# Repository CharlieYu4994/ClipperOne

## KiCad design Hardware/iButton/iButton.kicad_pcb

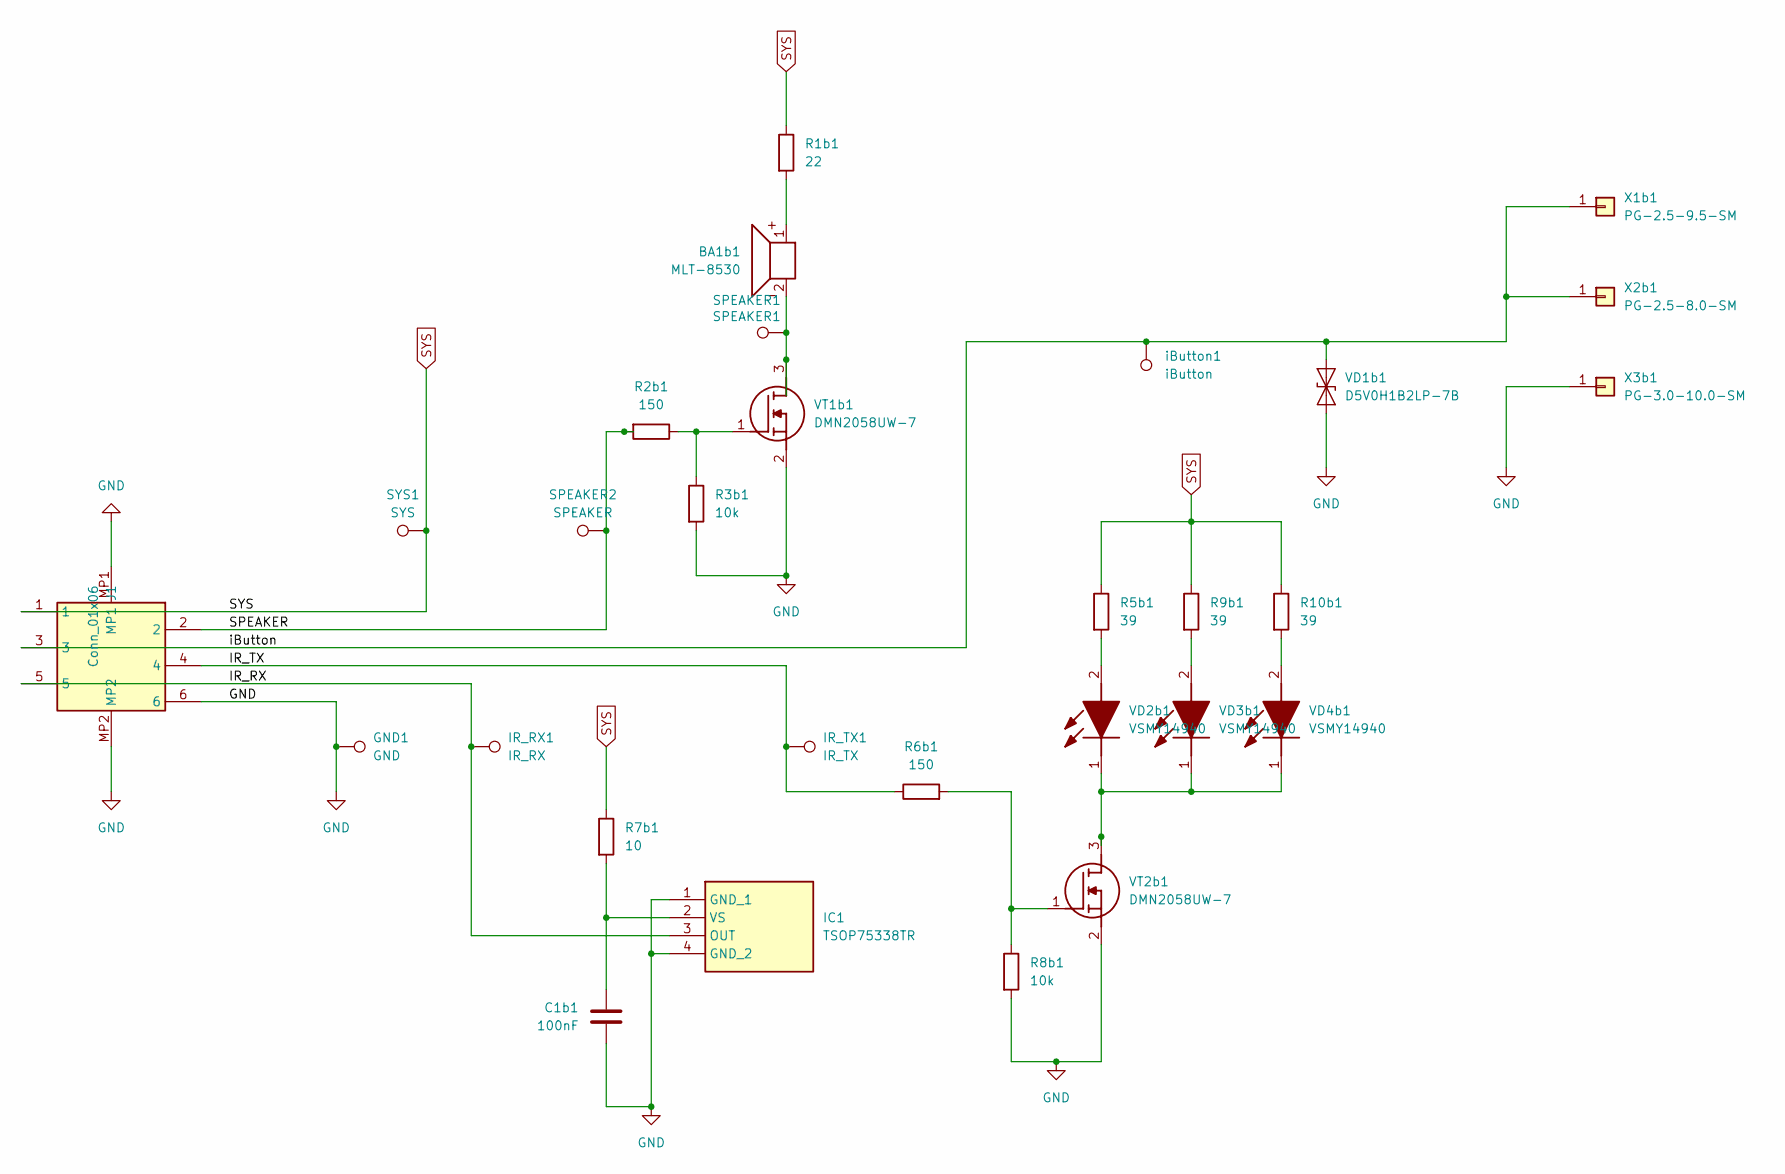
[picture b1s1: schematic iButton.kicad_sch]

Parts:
BA1b1: MLT-8530; MLT8530
C1b1: 100nF; C_0402_1005Metric
GND1: GND; TestPoint_Pad_D1.0mm
IC1: TSOP75338TR; Manufacturer_Part_Number TSOP75338TR; Mouser Part Number 78-TSOP75338TR
IR_RX1: IR_RX; TestPoint_Pad_D1.0mm
IR_TX1: IR_TX; TestPoint_Pad_D1.0mm
J1: Conn_01x06; AFC11S06ICC00; Manufacturer_Part_Number AFC11-S06ICC-00
R1b1: 22; R_0402_1005Metric
R2b1, R6b1: 150; R_0402_1005Metric
R3b1, R8b1: 10k; R_0402_1005Metric
R5b1, R9b1, R10b1: 39; R_0402_1005Metric
R7b1: 10; R_0402_1005Metric
SPEAKER1: SPEAKER1; TestPoint_Pad_D1.0mm
SPEAKER2: SPEAKER; TestPoint_Pad_D1.0mm
SYS1: SYS; TestPoint_Pad_D1.0mm
VD1b1: D5V0H1B2LP-7B; D5V0H1B2LP7B
VD2b1, VD3b1, VD4b1: VSMY14940; LEDC3012X261N; Manufacturer_Part_Number VSMY14940; Mouser Part Number 782-VSMY14940
VT1b1, VT2b1: DMN2058UW-7; SOT65P210X110-3N; Manufacturer_Part_Number AO3400A
X1b1: PG-2.5-9.5-SM; TestPoint_Pad_D2.0mm
X2b1: PG-2.5-8.0-SM; TestPoint_Pad_D2.0mm
X3b1: PG-3.0-10.0-SM; TestPoint_Pad_D2.0mm
iButton1: iButton; TestPoint_Pad_D1.0mm

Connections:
/IR_RX: IC1.3 (OUT), IR_RX1.1, J1.5
/IR_TX: IR_TX1.1, J1.4, R6b1.1
/SPEAKER: J1.2, R2b1.2, SPEAKER2.1
/iButton: J1.3, VD1b1.2 (A2), X1b1.1, X2b1.1, iButton1.1
GND: C1b1.2, GND1.1, IC1.1 (GND_1), IC1.4 (GND_2), J1.6, J1.MP1, J1.MP2, R3b1.2, R8b1.2, VD1b1.1 (A1), VT1b1.2 (S), VT2b1.2 (S), X3b1.1
unnamed: BA1b1.1 (+), R1b1.2
unnamed: BA1b1.2 (-), SPEAKER1.1, VT1b1.3 (D)
unnamed: C1b1.1, IC1.2 (VS), R7b1.2
unnamed: R5b1.2, VD2b1.2 (A)
unnamed: VD2b1.1 (K), VD3b1.1 (K), VD4b1.1 (K), VT2b1.3 (D)
unnamed: R9b1.2, VD3b1.2 (A)
unnamed: R10b1.2, VD4b1.2 (A)
unnamed: R2b1.1, R3b1.1, VT1b1.1 (G)
unnamed: R6b1.2, R8b1.1, VT2b1.1 (G)
SYS: J1.1, R1b1.1, R5b1.1, R7b1.1, R9b1.1, R10b1.1, SYS1.1

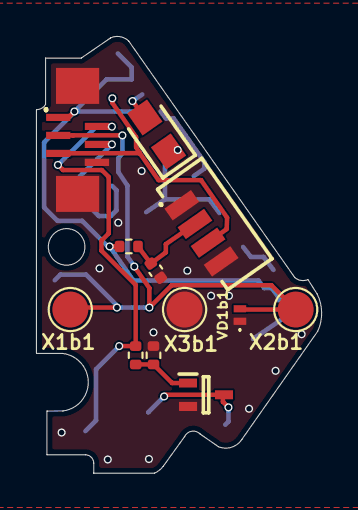
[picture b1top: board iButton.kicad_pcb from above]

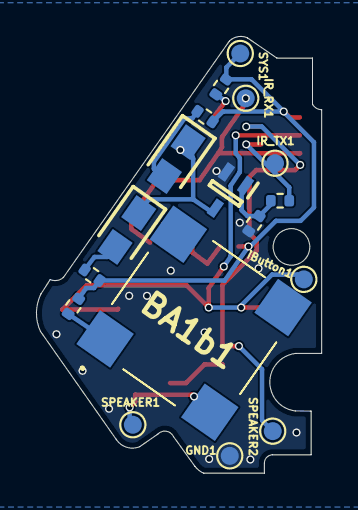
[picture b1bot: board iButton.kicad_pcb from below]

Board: 2 copper layers, 15.8 x 24.3 mm, 29 parts (17 on the bottom side), 15 nets.

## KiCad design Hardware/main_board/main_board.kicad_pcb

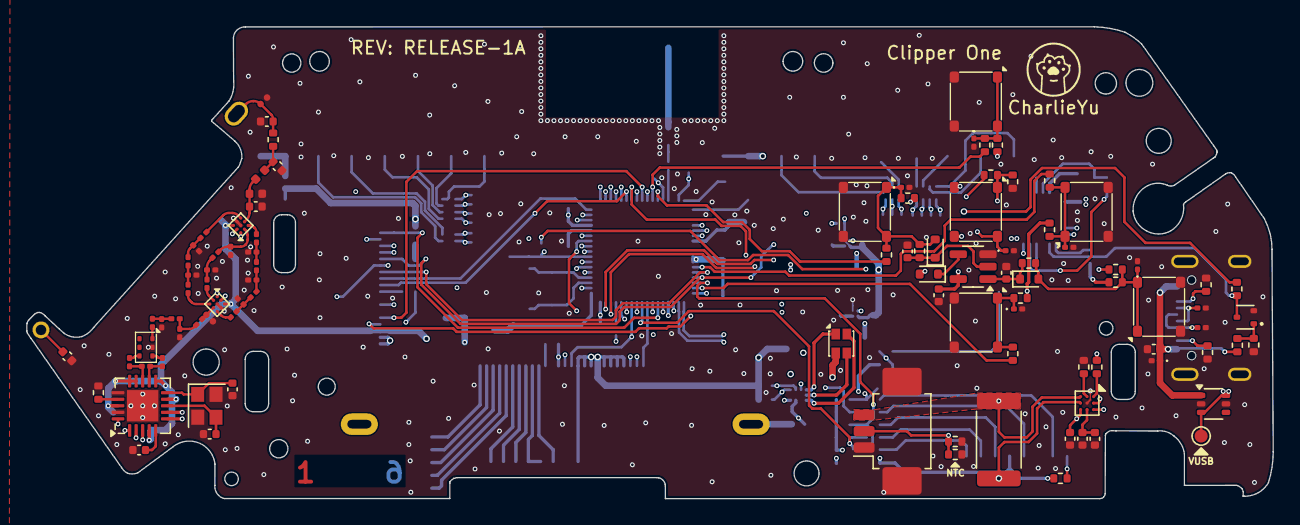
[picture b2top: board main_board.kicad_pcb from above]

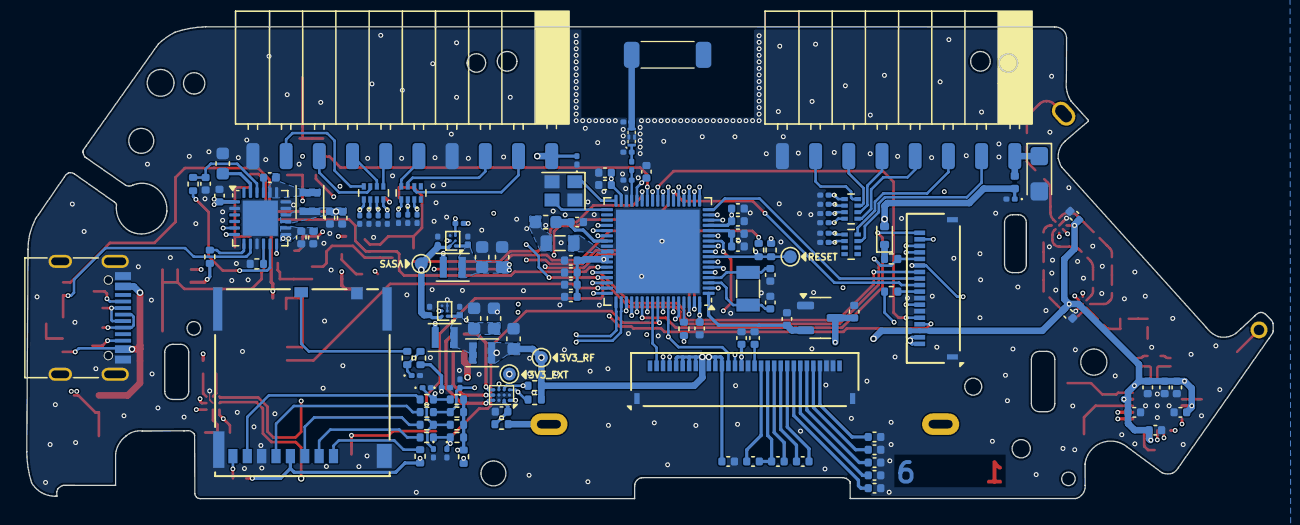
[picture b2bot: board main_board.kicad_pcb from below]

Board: 6 copper layers, 95.4 x 36.1 mm, 238 parts (136 on the bottom side), 165 nets.

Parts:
AE1: CrossAir C3; CrossAir-C3
AE2: Sub 1G; ANT_SUB1G
C1, C7, C11, C28: 4.7uF; C_0402_1005Metric
C2, C3, C4, C5, C8, C13, C40, C41, C42, C43, C44, C45, C46, C66, C69, C80, C82: 100nF; C_0402_1005Metric
C6, C70: 100pF; C_0402_1005Metric
C9, C12, C18, C24, C32, C33: 1uF; C_0402_1005Metric
C10, C54, C55: 10nF; C_0402_1005Metric
C14: 0.3pF; C_0201_0603Metric
C15: 0.8pF; C_0201_0603Metric
C16, C17: 18pF; C_0402_1005Metric
C19: 47nF; C_0402_1005Metric
C20, C21, C26, C27, C67, C68: 10uF; C_0402_1005Metric
C22: 470nF; C_0402_1005Metric
C23, C73, C79: 2.2uF; C_0402_1005Metric
C25, C31, C37, C38: 10uF; C_0603_1608Metric
C29, C35: 1uF; C_0201_0603Metric
C30, C36: 4.7uF; C_0603_1608Metric
C34, C39: 2.2uF; C_0201_0603Metric
C47, C49: 100pF; C_0201_0603Metric
C48: 0.6pF; C_0201_0603Metric
C50, C56, C57, C65: TBD; C_0201_0603Metric
C51: 1.2pF; C_0201_0603Metric
C52, C53: 9pF; C_0402_1005Metric
C58, C62, C63, C71, C72, C74, C75, C76, C77, C78, C83: TBD; C_0402_1005Metric
C59, C60: 10pF; C_0201_0603Metric
C61: 22pF; C_0201_0603Metric
C64: 8.2pF; C_0201_0603Metric
C81: TBD; CP_EIA-3216-18_Kemet-A
D1, D2, D3, D4, D5, D6, D11, D12, D13, D14, D15, D16, D18, D19, D20, D21, D22, D23, D24, D25, D26, D27, D28, D29, D30, D31, D32, D33, D34, D35: TVS; D_0201_0603Metric
D7, D8, D9, D17: 1N4148; D_SOD-523
D10: LED_RBGA; LTST-C19HE1WT_LTO
F1: 2A; Fuse_0402_1005Metric
FL1: DLF162500LT-5028A1; DLF162500LT
J1: BATT; Molex_PicoBlade_53261-0371_1x03-1MP_P1.25mm_Horizontal
J2: LCD; CONN30x1_FH34SRJ-30S-0.5SH50_HIR
J3: BACK_LIGHT; ERC12864FAMF03
J4: SD; CONN_503398-1892_MOL
J5: NFC; CONN18x1_FH34SRJ-18S-0.5SH50_HIR
J6: EXT1; PinSocket_1x10_P2.54mm_Horizontal_SMD
J7: EXT0; PinSocket_1x08_P2.54mm_Horizontal_SMD
J8: USB_C; USB_C_Receptacle_G-Switch_GT-USB-7010ASV
L1: 10uH; L_0603_1608Metric
L2: 10uH; L_0805_2012Metric
L3, L20, L21: 2.7nH; L_0201_0603Metric
L4: 1uH; L_Murata_DFE201610P
L5, L6, L7: 470nH; L_Murata_DFE201610P
L8: 3.3nH; L_0201_0603Metric
L9: 6.8nH; L_0201_0603Metric
L10, L11, L13, L15, L19: 0; L_0201_0603Metric
L12: 56nH; L_0201_0603Metric
L14: 27nH; L_0201_0603Metric
L16: 22nH; L_0201_0603Metric
L17: 2.2nH; L_0402_1005Metric
L18: TBD; L_0402_1005Metric
Q1: DMN313DLT; SOT-523
R1, R45, R46, R47, R50: 51R; R_0402_1005Metric
R2, R3, R8, R11, R12, R14, R19, R20, R21, R22, R23, R30, R31: 10K; R_0402_1005Metric
R4: 470R; R_0402_1005Metric
R5: 10m; R_2512_6332Metric
R6, R7, R51, R52: 5.1K; R_0402_1005Metric
R9: 5.23K; R_0402_1005Metric
R10: 30.1K; R_0402_1005Metric
R13: 100R; R_0402_1005Metric
R15: 10K; R_0201_0603Metric
R16: 0R; R_0201_0603Metric
R17: 56K/0.1%; R_0402_1005Metric
R18, R35, R36: 0R; R_0402_1005Metric
R24, R25, R26, R27, R28, R29, R33: 330R; R_0402_1005Metric
R32, R34: 100K; R_0402_1005Metric
R37, R38, R39, R40, R41, R42, R43: 47K; R_0402_1005Metric
R44, R48: 150R; R_0402_1005Metric
R49: 1K; R_0402_1005Metric
RFF**: CharlieYu; charlieyu
RN1, RN2, RN3, RN4: 51R; R_Array_Concave_4x0402
SW1: OK; SW_Push_SPST_NO_Alps_ SKRM
SW2: BACK; SW_Push_SPST_NO_Alps_ SKRM
SW3: RIGHT; SW_Push_SPST_NO_Alps_ SKRM
SW4: LEFT; SW_Push_SPST_NO_Alps_ SKRM
SW5: UP; SW_Push_SPST_NO_Alps_ SKRM
SW6: DOWN; SW_Push_SPST_NO_Alps_ SKRM
T1: B0310J50100AHF
TP1: RST; TestPoint_Pad_D1.0mm
TP12: 5V_USB; TestPoint_Pad_D1.0mm
TP18: VSYS; TestPoint_Pad_D1.0mm
TP20: 3V3_MAIN; TestPoint_Pad_D1.0mm
TP21: 3V3_EXT; TestPoint_Pad_D1.0mm
TP32: Balun; TP_DP
TP33: CC1101_OUT; TP_DP
U1: STM32WB55RGVx; QFN-68-1EP_8x8mm_P0.4mm_EP6.4x6.4mm
U2: BQ27220YZFR; Texas_DSBGA-9_1.62mmx1.58mm_Layout3x3_P0.5mm
U3: BQ25896RTWR; Texas_RTW_WQFN-24-1EP_4x4mm_P0.5mm_EP2.7x2.7mm
U4: RS3221-3.3YF3; SOT-23-3
U5: LM66100DCK; SOT-363_SC-70-6
U6, U7: LM3281YFQR; BGA-6_2x3_1.16x1.435mm
U8: CC1101RGP; Texas_RGP0020H_VQFN-20-1EP_4x4mm_P0.5mm_EP2.4x2.4mm
U9, U10: BGS13S4N9E6327XTSA1; BGA-9_3x3_1.2x1.2mm
U11: NC7SZ32M5X; SOT-23-5
U12: LP5562TMX; BGA-12_4x3_1.6x1.2mm
Y1: 32MHz; Crystal_SMD_2520-4Pin_2.5x2.0mm
Y2: 32.768K; Crystal_SMD_3215-2Pin_3.2x1.5mm
Y3: 26MHz; Crystal_SMD_2520-4Pin_2.5x2.0mm

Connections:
+3.3V: C1.2, C2.2, C3.2, C4.2, C5.2, C6.2, C7.2, C8.2, C9.2, C10.2, C38.2, C40.2, C41.2, C42.2, C43.2, C44.2, C45.2, C54.1, C55.1, C66.1, C69.2, C70.2, J2.5, J2.6, J2.7, J2.8, J2.9, J2.10, J2.11, J2.12, J2.15, J5.3, L7.2, R2.1, R6.2, R7.2, R8.2, R15.1, R19.2, R20.2, R21.2, R22.2, R23.2, R31.2, SW1.2, TP20.1, U1.14 (VDDA), U1.30 (VDD), U1.33 (VDDRF), U1.44 (VDDSMPS), U1.45 (VDD), U1.55 (VDDUSB), U1.68 (VDD), U8.4 (DVDD), U8.9 (AVDD), U8.11 (AVDD), U8.14 (AVDD), U8.15 (AVDD), U8.18 (DGUARD), U9.A3 (VDD), U10.A3 (VDD), U11.5 (VCC)
+3.3V_EXT: C30.2, C31.2, C34.2, D18.2 (A2), J6.1, L5.2, R36.1, TP21.1, U6.A1 (FB)
+3.3V_LDO: C33.2, U1.1 (VBAT), U4.2 (VOUT)
/Buttons/BACK: D2.1 (A1), D7.2 (A), R19.1, R25.2, R32.2, SW2.1
/Buttons/BUTTON_BACK: R25.1, U1.2 (PC13), U3.12 (QON_N)
/Buttons/BUTTON_DOWN: R29.1, U1.50 (PC6)
/Buttons/BUTTON_LEFT: R27.1, U1.29 (PB11)
/Buttons/BUTTON_OK: R24.1, U1.5 (PH3)
/Buttons/BUTTON_RIGHT: R26.1, U1.46 (PB12)
/Buttons/BUTTON_UP: R28.1, U1.28 (PB10)
/Buttons/LEFT: D4.1 (A1), D9.2 (A), R21.1, R27.2, R34.2, SW4.1
/Buttons/RESET: R31.1, R33.1, TP1.1, U1.8 (NRST), U12.C3 (EN_VCC)
/CC1101/CC1101_CS: U1.61 (PD0), U8.7 (CSN)
/CC1101/CC1101_G0: U1.16 (PA1), U8.6 (GDO0)
/CC1101/CC1101_UBAL: R16.2, TP32.1, U9.C2 (RFIN)
/CC1101/RF_SW_0: U1.25 (PC4), U9.A2 (V2), U10.A1 (V1)
/CC1101/RF_SW_1: U8.3 (GD02), U9.A1 (V1), U10.A2 (V2)
/CC1101/SPI_R_MISO: R50.1, U1.64 (PB4), U8.2 (SO)
/CC1101/SPI_R_MOSI: J5.13, R1.2, U8.20 (SI)
/CC1101/SPI_R_SCK: J5.7, U1.20 (PA5), U8.1 (SCLK)
/LCD/DISPLAY_CS: J2.2, U1.59 (PC11)
/LCD/DISPLAY_DI: J2.4, U1.39 (PB1)
/LCD/DISPLAY_RST: J2.3, U1.38 (PB0)
/LCD/LCD_LED: J3.1 (K), U12.A1 (W)
/LCD/SPI_D_MOSI: D12.1 (A1), J2.14, R38.1, R45.1, U1.49 (PB15)
/LCD/SPI_D_SCK: D13.1 (A1), J2.13, R39.1, R46.1, U1.62 (PD1)
/MCU/D+: D35.1 (A1), J8.A6 (D+), J8.B6 (D+), U1.53 (PA12)
/MCU/D-: D34.1 (A1), J8.A7 (D-), J8.B7 (D-), U1.52 (PA11)
/MCU/I2C_SCL: R7.1, U1.24 (PA9), U2.A3 (SCL), U3.5 (SCL), U12.C2 (SCL)
/MCU/I2C_SDA: R6.1, U1.51 (PA10), U2.A2 (SDA), U3.6 (SDA), U12.C1 (SDA)
/MCU/IR_RX: J5.17, U1.15 (PA0)
/MCU/IR_TX: J5.16, U1.7 (PB9)
/MCU/NFC_CS: J5.4, U1.40 (PE4)
/MCU/PA4: D22.1 (A1), RN3.8, U1.19 (PA4)
/MCU/PA6: D21.1 (A1), RN1.5, U1.21 (PA6)
/MCU/PA7: D20.1 (A1), RN1.6, U1.22 (PA7)
/MCU/PB2: D24.1 (A1), RN3.6, U1.27 (PB2)
/MCU/PB3: D23.1 (A1), RN3.7, U1.63 (PB3)
/MCU/PC0: D31.1 (A1), RN4.6, U1.9 (PC0)
/MCU/PC1: D30.1 (A1), RN4.7, U1.10 (PC1)
/MCU/PC3: D25.1 (A1), RN3.5, U1.12 (PC3)
/MCU/PERI_EN: R15.2, U1.18 (PA3), U6.C1 (EN)
/MCU/RFID_CARRIER: J5.18, U1.57 (PA15)
/MCU/RFID_OUT: J5.12, U1.47 (PB13)
/MCU/RFID_PULL: J5.11, U1.17 (PA2)
/MCU/RFID_RF_IN: J5.5, U1.26 (PC5)
/MCU/SD_CD: D15.1 (A1), R41.1, R48.1, U1.58 (PC10)
/MCU/SD_CS: D11.1 (A1), R37.1, R44.1, U1.60 (PC12)
/MCU/SPEAKER: J5.15, U1.6 (PB8)
/MCU/SPI_D_MISO: D14.1 (A1), R40.1, R47.1, U1.11 (PC2)
/MCU/SWCLK: D26.1 (A1), RN2.7, U1.56 (PA14)
/MCU/SWDIO: D27.1 (A1), RN2.6, U1.54 (PA13)
/MCU/UART1_RX: D29.1 (A1), RN4.8, U1.67 (PB7)
/MCU/UART1_TX: D28.1 (A1), RN2.5, U1.66 (PB6)
/MCU/VIBRO: J5.10, U1.23 (PA8)
/MCU/iBTN: D32.1 (A1), J5.14, R49.2, RN4.5, U1.48 (PB14)
/Power/BAT+: C18.2, J1.3, R5.2, U2.C1 (SRP), U2.C3 (BAT)
BAT: C26.2, C27.2, C32.2, R5.1, U2.C2 (SRN), U3.13 (BAT), U3.14 (BAT), U4.3 (VIN)
GND: C1.1, C2.1, C3.1, C4.1, C5.1, C6.1, C7.1, C8.1, C9.1, C10.1, C11.1, C12.1, C13.1, C14.1, C15.1, C16.1, C17.1, C18.1, C20.1, C21.1, C22.1, C23.1, C24.1, C25.1, C26.1, C27.1, C28.1, C29.1, C30.1, C31.1, C32.1, C33.1, C34.1, C35.1, C36.1, C37.1, C38.1, C39.1, C40.1, C41.1, C42.1, C43.1, C44.1, C45.1, C46.2, C50.1, C51.1, C52.1, C53.1, C54.2, C55.2, C56.2, C57.2, C58.2, C59.1, C60.1, C61.1, C62.1, C63.1, C64.1, C65.1, C66.2, C67.1, C68.1, C69.1, C70.1, C71.1, C75.1, C76.1, C77.1, C78.1, C79.1, C80.2, C81.2, C82.2, C83.1, D1.2 (A2), D2.2 (A2), D3.2 (A2), D4.2 (A2), D5.2 (A2), D6.2 (A2), D11.2 (A2), D12.2 (A2), D13.2 (A2), D14.2 (A2), D15.2 (A2), D16.2 (A2), D18.1 (A1), D19.2 (A2), D20.2 (A2), D21.2 (A2), D22.2 (A2), D23.2 (A2), D24.2 (A2), D25.2 (A2), D26.2 (A2), D27.2 (A2), D28.2 (A2), D29.2 (A2), D30.2 (A2), D31.2 (A2), D32.2 (A2), D33.2 (A2), D34.2 (A2), D35.2 (A2), FL1.2 (GND), FL1.4 (GND), J1.1, J1.MP (MountPin), J2.16, J2.28, J2.29, J2.MP (MountPin), J4.6 (VSS), J4.10 (SHIELD), J5.6, J5.8, J5.MP (MountPin), J6.4, J6.10, J7.8, J8.A1 (GND), J8.A12 (GND), J8.B1 (GND), J8.B12 (GND), J8.S1 (SHIELD), L18.1, L21.1, Q1.2 (S), R3.2, R4.1, R10.1, R11.1, R14.1, R17.2, R30.1, R51.1, R52.1, SW2.2, SW3.2, SW4.2, SW5.2, SW6.2, T1.2 (GND), TP32.2, TP33.2, U1.32 (VSSRF), U1.42 (VSSSMPS), U1.69 (VSS), U2.B2 (VSS), U3.2 (PSEL), U3.9 (CE_N), U3.17 (PGND), U3.18 (PGND), U3.25 (PAD), U4.1 (GND), U5.2 (GND), U5.5 (ST), U6.C2 (EPAD), U7.B1 (MODE), U7.C1 (EN), U7.C2 (EPAD), U8.16 (GND), U8.19 (GND), U8.21 (EPAD), U9.B2 (GND), U9.B3 (DGND), U10.B2 (GND), U10.B3 (DGND), U11.3 (GND), U12.A3 (CLK_32K), U12.B1 (A1), U12.B2 (A0), U12.B3 (GND), Y1.2, Y1.4, Y3.2, Y3.4
unnamed: AE1.1 (FEED), FL1.3 (OUT), L21.2
unnamed: AE2.1 (A), C63.2, R18.2, TP33.1
unnamed: AE2.2 (Shield), C83.2
unnamed: C47.2, T1.4 (Bal)
unnamed: C49.2, T1.3 (Bal)
unnamed: C50.2, L8.2, L9.1
unnamed: C51.2, L9.2, R16.1
unnamed: C56.1, L10.2, L11.1
unnamed: C57.1, L11.2, L12.1
unnamed: C59.2, L13.2, L14.1
unnamed: C60.2, L14.2, L15.1
unnamed: C61.2, L15.2, L16.1
unnamed: C62.2, L17.2, R18.1
unnamed: C64.2, L19.2, L20.1
unnamed: D1.1 (A1), R24.2, R30.2, SW1.1
unnamed: D3.1 (A1), R20.1, R26.2, SW3.1
unnamed: D5.1 (A1), R22.1, R28.2, SW5.1
unnamed: D6.1 (A1), R23.1, R29.2, SW6.1
unnamed: C67.2, D7.1 (K), R32.1, U11.1
unnamed: D8.2 (A), R33.2
unnamed: D8.1 (K), U11.4
unnamed: C68.2, D9.1 (K), R34.1, U11.2
unnamed: D10.2 (BK), U12.A4 (B)
unnamed: D10.3 (GK), U12.B4 (G)
unnamed: D10.1 (RK), U12.C4 (R)
unnamed: D16.1 (A1), J4.4 (VDD), R36.2, R37.2, R38.2, R39.2, R40.2, R41.2, R42.2, R43.2
unnamed: D17.1 (K), R49.1
unnamed: C14.2, FL1.1 (IN), L3.1
unnamed: J1.2, R9.2, R10.2, R11.2, U3.11 (TS)
unnamed: C71.2, J2.17
unnamed: C72.2, J2.18
unnamed: C72.1, C73.2, J2.19
unnamed: C73.1, J2.20
unnamed: C74.2, J2.21
unnamed: C74.1, J2.22
unnamed: C75.2, J2.23
unnamed: C76.2, J2.24
unnamed: C77.2, J2.25
unnamed: C78.2, J2.26
unnamed: C79.2, J2.27
unnamed: J3.2 (A), R35.1
unnamed: J4.5 (CLK), R46.2
unnamed: J4.3 (CMD), R45.2
unnamed: J4.7 (DAT0), R47.2
unnamed: J4.8 (DAT1), R42.1
unnamed: J4.1 (DAT2), R43.1
unnamed: J4.2 (DAT3/CD), R44.2
unnamed: J4.9 (DET), R48.2
unnamed: J5.9, R50.2
unnamed: J6.2, RN2.2
unnamed: J6.3, RN2.3
unnamed: J6.5, RN2.4
unnamed: J6.6, RN4.1
unnamed: J6.7, RN4.2
unnamed: J6.8, RN4.3
unnamed: J6.9, RN4.4
unnamed: C81.1, F1.2, J7.1
unnamed: J7.2, RN1.3
unnamed: J7.3, RN1.4
unnamed: J7.4, RN3.1
unnamed: J7.5, RN3.2
unnamed: J7.6, RN3.3
unnamed: J7.7, RN3.4
unnamed: J8.A5 (CC1), R52.2
unnamed: J8.B5 (CC2), R51.2
unnamed: L1.2, L2.1
unnamed: Q1.3 (D), R12.2, U3.8 (OTG_IUSB)
unnamed: Q1.1 (G), R13.2, R14.2
unnamed: L8.1, T1.1 (Unbal)
unnamed: U1.35 (OSC_IN), Y1.3
unnamed: U1.34 (OSC_OUT), Y1.1
unnamed: R1.1, U1.65 (PB5)
unnamed: C16.2, U1.3 (PC14), Y2.2
unnamed: C17.2, U1.4 (PC15), Y2.1
unnamed: C15.2, L3.2, U1.31 (RF1)
unnamed: C11.2, L1.1, U1.41 (VFBSMPS)
unnamed: L2.2, U1.43 (VLXSMPS)
unnamed: C12.2, C13.2, U1.13 (VREF+)
unnamed: R3.1, U2.B1 (BIN)
unnamed: R2.2, U2.A1 (GPOUT)
unnamed: C22.2, C23.2, U2.B3 (VDD)
unnamed: C19.1, U3.21 (BTST)
unnamed: R4.2, U3.10 (ILIM)
unnamed: R8.1, U3.7 (INT)
unnamed: C25.2, U3.23 (PMID)
unnamed: C28.2, R9.1, U3.22 (REGN)
unnamed: L5.1, U6.B2 (SW)
unnamed: C36.2, C37.2, C39.2, L6.2, L7.1, U7.A1 (FB)
unnamed: L6.1, U7.B2 (SW)
unnamed: C46.1, U8.5 (DCOUPL)
unnamed: R17.1, U8.17 (RBIAS)
unnamed: C47.1, C48.1, U8.13 (RF_N)
unnamed: C48.2, C49.1, U8.12 (RF_P)
unnamed: C52.2, U8.8 (XOSC_Q1), Y3.3
unnamed: C53.2, U8.10 (XOSC_Q2), Y3.1
unnamed: L10.1, U9.C1 (RF1)
unnamed: L13.1, U9.C3 (RF2)
unnamed: L19.1, U9.B1 (RF3)
unnamed: L16.2, U10.C1 (RF1)
unnamed: L12.2, U10.C3 (RF2)
unnamed: C65.2, L20.2, U10.B1 (RF3)
unnamed: C58.1, L17.1, L18.2, U10.C2 (RFIN)
SW: C19.2, L4.1, U3.19 (SW), U3.20 (SW)
VBUS: C82.1, D33.1 (A1), J8.A4 (VBUS), J8.A9 (VBUS), J8.B4 (VBUS), J8.B9 (VBUS), R13.1, U5.1 (VIN)
VSYS: C20.2, C21.2, C29.2, C35.2, C80.1, D10.4 (A), L4.2, R12.1, R35.2, TP18.1, U3.15 (SYS), U3.16 (SYS), U6.A2 (VIN), U6.B1 (MODE), U7.A2 (VIN), U12.A2 (VDD)
VUSB: C24.2, D17.2 (A), D19.1 (A1), F1.1, J5.1, J5.2, TP12.1, U3.1 (VBUS), U5.3 (~CE), U5.6 (VOUT)

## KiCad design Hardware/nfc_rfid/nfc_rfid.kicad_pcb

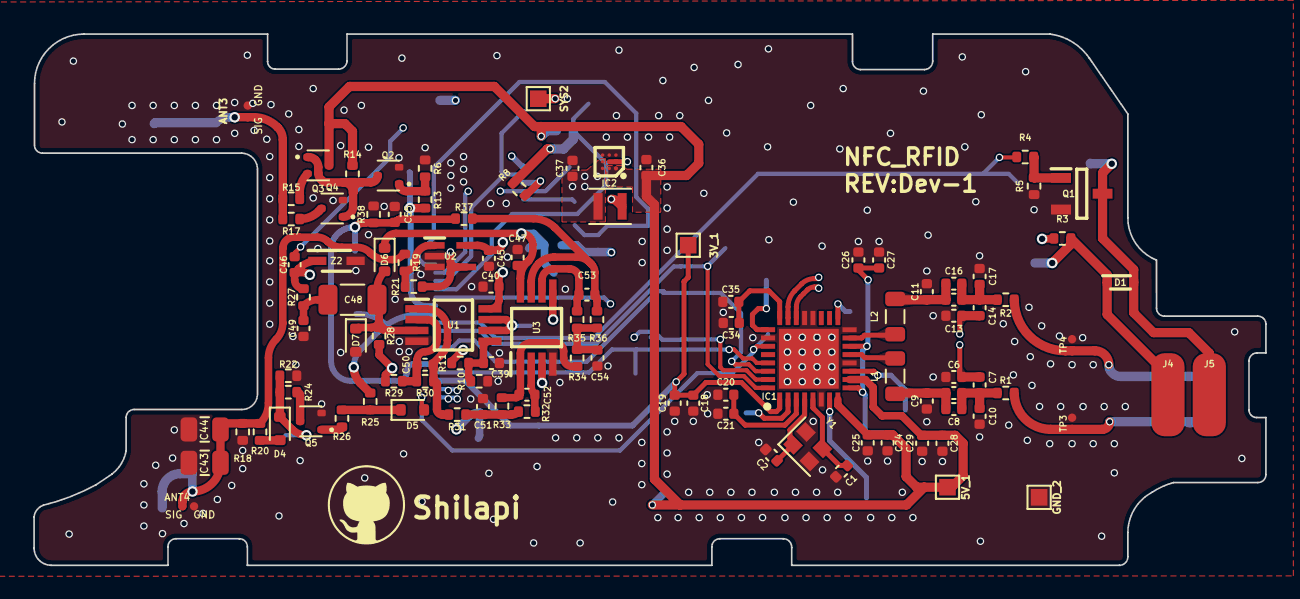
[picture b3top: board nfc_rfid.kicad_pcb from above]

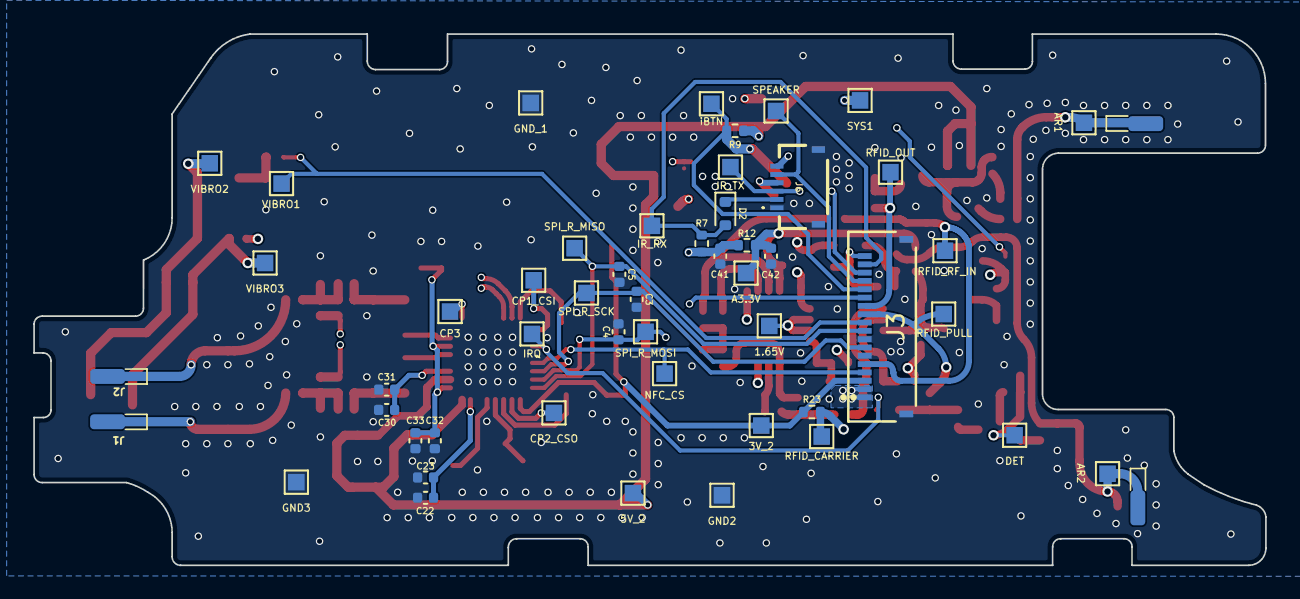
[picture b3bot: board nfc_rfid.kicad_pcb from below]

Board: 4 copper layers, 74.1 x 32.0 mm, 158 parts (52 on the bottom side), 68 nets.

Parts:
C1, C2: 6pF; C_0402_1005Metric
C3, C4, C5, C12, C15, C50: C; C_0402_1005Metric
C6, C8, C13, C16, C52, C53, C55: 100pF; C_0402_1005Metric
C7, C14: 10pF; C_0402_1005Metric
C9, C11: 680pF; C_0402_1005Metric
C10, C17: 62pF; C_0402_1005Metric
C18, C20, C22, C24, C26, C28, C30, C32, C34, C46: 10nF; C_0402_1005Metric
C19, C21, C23, C25, C27, C29, C31, C33, C35: 2.2uF; C_0402_1005Metric
C36: 22uF; C_0402_1005Metric
C37: 10uF; C_0402_1005Metric
C39, C41, C42: 1uF; C_0402_1005Metric
C40, C45, C47: 100nF; C_0402_1005Metric
C43: 3.3nF; C_0805_2012Metric
C44: C; C_0805_2012Metric
C48: 220nF; C_1206_3216Metric
C49: 1nF; C_0402_1005Metric
C51, C54: 4.7nF; C_0402_1005Metric
D1: 1N4148X-TP; SODFL1608X70N
D2, D4, D5, D6, D7: 1N4148WT; D_SOD-523
IC1: ST25R3916-AQWT; QFN50P500X500X100-33N-D
IC2: FAN48610UC50X; BGA9C40P3X3_122X122X62
J1, J2, J7, J8: BW0033AG-L3.4W0.9H1.8; SMD_L3.4-W0.9
J3: HC-FPC-05-09-18RLTAG; CONN18x1_FH34SRJ-18S-0.5SH50_HIR
J4: +; TestPoint_Pad_3.0x2.0mm_round_corner_no_silkscreen
J5: -; TestPoint_Pad_3.0x2.0mm_round_corner_no_silkscreen
J6: AFH34-S06FIA-1H; AFH34S06FIA1H
L1, L2: 270nH; L_0805_2012Metric
L3: 470nH; L_Murata_DFE201610P
Q1: AO3400A; SOT95P280X125-3N
Q2, Q4: DMN2004TK-7; SOT-523
Q3: DMP2004TK-7; SOT-523
Q5: DMN5L06TK-7; SOT-523
R1, R2: 0Ω; R_0402_1005Metric
R3: 22; R_0402_1005Metric
R4: 150; R_0402_1005Metric
R5, R6, R7, R23, R33, R36: 10k; R_0402_1005Metric
R8, R13: 51; R_0402_1005Metric
R9: 47k; R_0402_1005Metric
R10, R11, R37: 33k; R_0402_1005Metric
R12: 10; R_0402_1005Metric
R14: 510; R_0402_1005Metric
R15, R17: 4.7; R_0402_1005Metric
R18, R21: R; R_0402_1005Metric
R19, R22: 330k; R_0402_1005Metric
R20: 0; R_0402_1005Metric
R24: 330; R_0402_1005Metric
R25, R26: 220; R_0402_1005Metric
R27: 5.1k; R_0402_1005Metric
R28: 1M; R_0402_1005Metric
R29, R31, R32, R34, R35: 1k; R_0402_1005Metric
R30: 4.7k; R_0402_1005Metric
R38: 20k; R_0402_1005Metric
TP1: CP1_CSI; TestPoint_Pad_1.0x1.0mm
TP2: CP2_CSO; TestPoint_Pad_1.0x1.0mm
TP3: ANT1; TP_DP
TP4: ANT2; TP_DP
TP5: CP3; TestPoint_Pad_1.0x1.0mm
TP6: IR_RX; TestPoint_Pad_1.0x1.0mm
TP7: IR_TX; TestPoint_Pad_1.0x1.0mm
TP8: SPEAKER; TestPoint_Pad_1.0x1.0mm
TP9: iBTN; TestPoint_Pad_1.0x1.0mm
TP10: SPI_R_MOSI; TestPoint_Pad_1.0x1.0mm
TP11: RFID_OUT; TestPoint_Pad_1.0x1.0mm
TP12: RFID_PULL; TestPoint_Pad_1.0x1.0mm
TP13: SPI_R_MISO; TestPoint_Pad_1.0x1.0mm
TP14: SPI_R_SCK; TestPoint_Pad_1.0x1.0mm
TP15: RFID_RF_IN; TestPoint_Pad_1.0x1.0mm
TP16: NFC_CS; TestPoint_Pad_1.0x1.0mm
TP17: VIBRO1; TestPoint_Pad_1.0x1.0mm
TP18: RFID_CARRIER; TestPoint_Pad_1.0x1.0mm
TP19: GND2; TestPoint_Pad_1.0x1.0mm
TP20: GND3; TestPoint_Pad_1.0x1.0mm
TP21: VIBRO3; TestPoint_Pad_1.0x1.0mm
TP22: VIBRO2; TestPoint_Pad_1.0x1.0mm
TP23: SYS1; TestPoint_Pad_1.0x1.0mm
TP24: SYS2; TestPoint_Pad_1.0x1.0mm
TP25: 5V_1; TestPoint_Pad_1.0x1.0mm
TP26: 5V_2; TestPoint_Pad_1.0x1.0mm
TP27: 3V_1; TestPoint_Pad_1.0x1.0mm
TP28: 3V_2; TestPoint_Pad_1.0x1.0mm
TP29: GND_1; TestPoint_Pad_1.0x1.0mm
TP30: GND_2; TestPoint_Pad_1.0x1.0mm
TP33: 1.65V; TestPoint_Pad_1.0x1.0mm
TP34: A3.3V; TestPoint_Pad_1.0x1.0mm
TP35: AR1; TestPoint_Pad_1.0x1.0mm
TP36: AR2; TestPoint_Pad_1.0x1.0mm
TP37: ANT3; TP_DP
TP38: ANT4; TP_DP
TP39: DET; TestPoint_Pad_1.0x1.0mm
TP40: IRQ; TestPoint_Pad_1.0x1.0mm
U1, U3: LMV358AIDGKR; SOP65P490X110-8N
U2: LMV331IDCKR; SOT65P210X110-5N
Y1: CF4027M12010001; Crystal_SMD_2016-4Pin_2.0x1.6mm
Z2: BZT52C33S-TP; SOD2512X115N

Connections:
+1.65V: R28.1, R29.2, TP33.1, U1.6 (-), U1.7, U3.3 (+), U3.5 (+)
+3.3V: C18.1, C19.1, C41.1, IC1.1 (VDD_IO), J3.3, R7.1, R12.1, R23.2, TP27.1, TP28.1
+5V: C24.1, C25.1, C28.1, C29.1, C36.1, IC1.8 (VDD), IC1.10 (VDD_TX), IC2.A1 (VOUT_1), IC2.A2 (VOUT_2), Q3.3 (D), R9.1, R14.1, TP25.1, TP26.1
/NFC/EXT_LM: IC1.17 (EXT_LM), TP5.1
/NFC/NFC_ANT1: J1.1, R1.2, TP3.1
/NFC/NFC_ANT2: J2.1, R2.2, TP4.1
/NFC/NFC_CS: IC1.29 (BSS), J3.4, TP16.1
/NFC/NFC_IRQ: D5.2 (A), IC1.27 (IRQ), TP40.1
/NFC/RFI_N: C13.1, C14.1, IC1.23 (RFI2)
/NFC/RFI_P: C6.1, C7.1, IC1.22 (RFI1)
/NFC/SPI_R_MISO: C5.1, IC1.32 (MISO), J3.9, TP13.1
/NFC/SPI_R_MOSI: C4.1, IC1.31 (MOSI), J3.13, TP10.1
/NFC/SPI_R_SCK: C3.1, IC1.30 (SCL), J3.7, TP14.1
/Peripheral/IR_RX: D2.2 (A), J3.17, R7.2, TP6.1
/Peripheral/RFID_CARRIER: C46.1, D4.1 (K), J3.18, R21.2, R22.1, R23.1, R24.2, R27.1, TP18.1, TP39.1, U2.4, Z2.1 (K)
/Peripheral/RFID_OUT: J3.12, R13.1, TP11.1
/Peripheral/RFID_PULL: J3.11, R25.1, TP12.1
/Peripheral/RFID_RF_IN: C55.2, J3.5, R37.2, R38.1, TP15.1
/Peripheral/iBTN: C46.2, J3.14, R8.1, R9.2, TP9.1
/RFID_iBTN/IR_TX: J3.16, J6.3, TP7.1
/RFID_iBTN/SPEAKER: J3.15, J6.5, TP8.1
/RFID_iBTN/TSOP_RX: D2.1 (K), J6.2
A+3.3V: C40.2, C42.1, C45.1, C47.2, D6.1 (K), R11.1, R12.2, TP34.1, U1.8 (V+), U2.5 (V+), U3.8 (V+)
GND: C1.1, C2.1, C3.2, C4.2, C5.2, C6.2, C9.2, C10.2, C11.2, C13.2, C17.1, C18.2, C19.2, C20.2, C21.2, C22.2, C23.2, C24.2, C25.2, C26.2, C27.2, C28.2, C29.2, C30.2, C31.2, C32.2, C33.2, C34.2, C35.2, C36.2, C37.2, C39.2, C40.1, C41.2, C42.2, C43.2, C44.2, C45.2, C47.1, C49.2, C51.1, C54.1, C55.1, D7.2 (A), IC1.6 (GND_D), IC1.12 (GND_DR_1), IC1.16 (GND_DR_2), IC1.20 (I2C_EN), IC1.21 (VSS), IC1.26 (GND_A), IC1.33 (EPAD), IC2.C1 (PGND_1), IC2.C2 (PGND_2), IC2.C3 (AGND), J3.6, J3.8, J3.19, J3.20, J6.1, J6.7 (MP1), J6.8 (MP2), Q1.2 (S), Q2.2 (S), Q4.2 (S), Q5.2 (S), R5.2, R6.2, R10.2, R18.2, R22.2, R38.2, TP3.2, TP4.2, TP19.1, TP20.1, TP29.1, TP30.1, TP37.2, TP38.2, U1.4 (V-), U2.2 (V-), U2.3 (-), U3.4 (V-), Y1.2, Y1.4, Z2.2 (A)
unnamed: C7.2, C8.2, C10.1, C12.2, R1.1
unnamed: C11.1, C15.1, C16.1, L2.2
unnamed: C8.1, C9.1, C12.1, L1.2
unnamed: C14.2, C15.2, C16.2, C17.2, R2.1
unnamed: C48.1, C49.1, R27.2
unnamed: C50.2, R30.1, R31.2, U1.1
unnamed: C51.2, R31.1, R32.2, R33.2
unnamed: C52.2, R33.1, R34.2, U3.1
unnamed: C53.2, R36.1, R37.1, U3.7
unnamed: C54.2, R34.1, R35.2, R36.2
unnamed: D1.2 (A), J5.1, Q1.3 (D), TP22.1
unnamed: D1.1 (K), J4.1, R3.2, TP21.1
unnamed: D4.2 (A), R20.2
unnamed: D5.1 (K), R25.2, R26.1
unnamed: C48.2, D6.2 (A), D7.1 (K), R28.2, U1.3 (+)
unnamed: C34.1, C35.1, IC1.24 (AGDC)
unnamed: IC1.25 (CSI), TP1.1
unnamed: IC1.2 (CSO), TP2.1
unnamed: IC1.13 (RFO1), L1.1
unnamed: IC1.15 (RFO2), L2.1
unnamed: C22.1, C23.1, IC1.7 (VDD_A)
unnamed: C30.1, C31.1, IC1.11 (VDD_AM)
unnamed: C20.1, C21.1, IC1.3 (VDD_D)
unnamed: C26.1, C27.1, C32.1, C33.1, IC1.9 (VDD_RF), IC1.14 (VDD_DR)
unnamed: C1.2, IC1.5 (XTI), Y1.3
unnamed: C2.2, IC1.4 (XTO), Y1.1
unnamed: IC2.B1 (SW_1), IC2.B2 (SW_2), L3.2
unnamed: J3.10, R4.1, TP17.1
unnamed: J6.4, R8.2
unnamed: C43.1, C44.1, J7.1, R18.1, R19.1, R20.1, TP36.1, TP38.1
unnamed: J8.1, R15.2, R17.1, TP35.1, TP37.1
unnamed: Q1.1 (G), R4.2, R5.1
unnamed: Q2.3 (D), Q3.1 (G), Q4.1 (G), R14.2
unnamed: Q2.1 (G), R6.1, R13.2
unnamed: Q3.2 (S), R15.1
unnamed: Q4.3 (D), R17.2
unnamed: Q5.3 (D), R24.1
unnamed: Q5.1 (G), R26.2
unnamed: C50.1, R29.1, R30.2, U1.2 (-)
unnamed: C39.1, R10.1, R11.2, U1.5 (+)
unnamed: R19.2, R21.1, U2.1 (+)
unnamed: C52.1, R32.1, U3.2 (-)
unnamed: C53.1, R35.1, U3.6 (-)
SYS: C37.1, IC2.A3 (VIN), IC2.B3 (EN), J3.1, J3.2, J6.6, L3.1, R3.1, TP23.1, TP24.1

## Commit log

2024-10-29 PCB: Re layout the iBTN board
2024-10-31 layout: finish the layout initially
2024-11-03 layout: cleanup tracks and vias
2024-11-03 PCB: iButton Fix missing hole
2024-11-04 layout: add some testpoints
2024-11-04 layout: move the back button
2024-11-04 silkscreen: start edit the silkscreens
2024-11-07 layout: change some routes
2024-11-07 footprint: fix sd card
2024-11-07 sch: change sd card footprint
2024-11-07 change the Package of D10 to LTST-C19HE1WT
2024-11-07 layout: change tf card postion
2024-11-07 misc: fix some fields
2024-11-07 layout: change LED footprint
2024-11-07 layout finish change LED footprint
2024-11-07 misc: fix conflict
2024-11-08 layout: add more stitching vias silkscreen: add more silkscreens
2024-11-08 layout: move the 2.4G ant away from the edge
2024-11-08 layout: optimise fab
2024-11-09 3D models rev4
2024-11-09 3D model: update screen_plate
2024-11-09 PCB: nfc_rfid: adjust vibro touch point
2024-11-09 PCB: nfc_rfid: add more stitching vias silkscreen: add more silkscreens
2024-11-10 footprint: change sd card footprint
2024-11-10 PCB: Update silkscreen for main board
2024-11-11 silkscreen: fix NTC silkscreen
2024-11-11 layout: move the dummy NTC to bottom
2024-11-11 silkscreen: change rev
